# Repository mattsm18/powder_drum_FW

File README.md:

# powder_drum_FW

Firmware for ENME891 - Industrial Project

# About

ENME891 is the capstone paper for the BE(Hons) degree at AUT. It is a year-long industrial project where students develop a real-world engineering solution.

### Project name: 
<b>Quanitfying the flowability of milk powders through the use of computer vision </b>

### Project members / responsibilities:
- Matthew Smith -> Embedded Firmware and Software Development, Mechanical Design, Electronic Design & Assembly
- Josh Russell -> Mechanical build and machining, MATLAB Computer vision modelling.

# Target
### Arduino Nano Every 
Potential for future, more capable targets due to using the PlatformIO framework

# Functionality
- Drive stepper motor from 0.1-70RPM with a closed-loop PID controller
- Control a 5V Relay Module
- Run bi-directional comms over serial to [powder_drum_SW](https://github.com/mattsm18/powder_drum_SW)

# Libraries

### StepperMotor
- Handles pin assignment, microstepping and internal velocity tracking
- Attaches a tick function to an ISR for atomic stepping

### AS5600 (Magnetic Encoder)
- Handles pin assignment and I2C comms with the encoder
- Determines current angular velocity of the motor
- Applies a 1st order discrete time filter

### PIDController
- Wraps all PID Controller functionality
- Handles dynamic Kp, Ki and Kd gains

### SerialManager
- Implements the packet framing protocol (SOF, header, payload, XOR CRC) over serial
- Validates and dispatches incoming GET/SET requests, returning ACK/NACK per the protocol

### PowderDrumProtocol
- Auto-generated from a single JSON source of truth (config/pd_comms_protocol_vX.X.json)
- Provides parameter metadata lookup (existence, access permissions) used by SerialManager

# Dependencies
- Use of the PlatformIO extension in VSCode for compiling, running and debugging code

# System Diagram

# Serial Comms Protocol
The powder drum implements a custom bi-directional serial comms protocol in 
the firmware and the software

This protocol includes ACKs, NACKs and a XOR CRC checksum to validate data integrity on the wire.

Fully implemented in the firmware, some work still to do for ACK and NACK handling in the software.

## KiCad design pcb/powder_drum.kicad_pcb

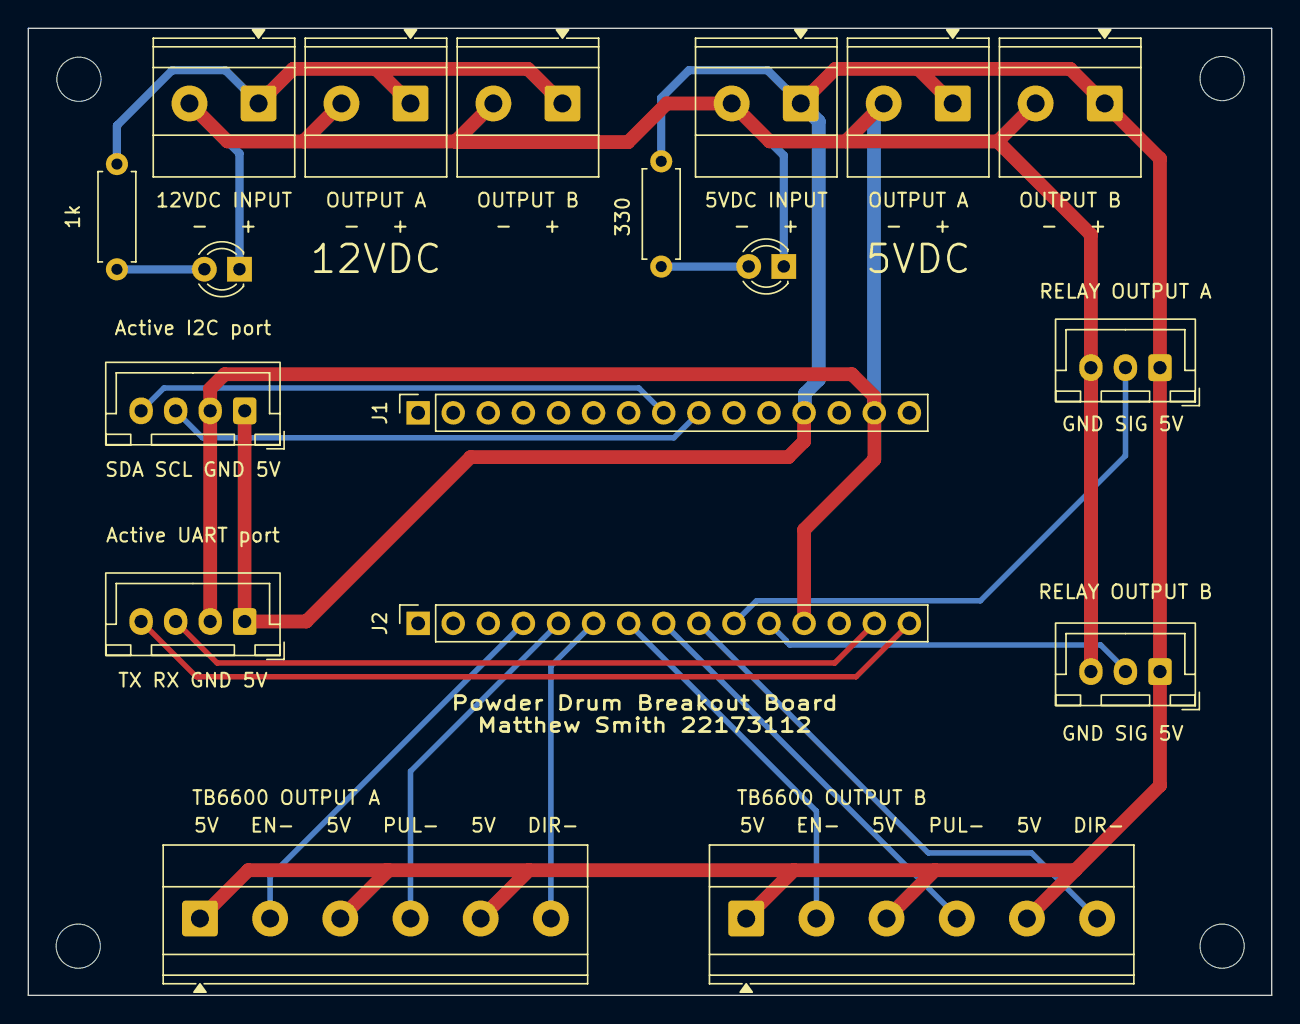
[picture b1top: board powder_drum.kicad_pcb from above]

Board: 2 copper layers, 90.0 x 70.0 mm, 18 parts (0 on the bottom side), 18 nets.

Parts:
D1, D2: LED; LED_D3.0mm
J1: Analog; PinSocket_1x15_P2.54mm_Vertical
J2: Digital; PinSocket_1x15_P2.54mm_Vertical
J3: 12VDC INPUT; TerminalBlock_Phoenix_MKDS-1,5-2_1x02_P5.00mm_Horizontal
J4: 5VDC INPUT; TerminalBlock_Phoenix_MKDS-1,5-2_1x02_P5.00mm_Horizontal
J5: TB6600 OUTPUT A; TerminalBlock_Phoenix_MKDS-1,5-6-5.08_1x06_P5.08mm_Horizont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
J6: TB6600 OUTPUT B; TerminalBlock_Phoenix_MKDS-1,5-6-5.08_1x06_P5.08mm_Horizont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
J7: Active UART port; JST_XH_B4B-XH-A_1x04_P2.50mm_Vertical
J8: RELAY OUTPUT B; JST_XH_B3B-XH-A_1x03_P2.50mm_Vertical
J9: RELAY OUTPUT A; JST_XH_B3B-XH-A_1x03_P2.50mm_Vertical
J10, J12: OUTPUT A; TerminalBlock_Phoenix_MKDS-1,5-2_1x02_P5.00mm_Horizontal
J11, J13: OUTPUT B; TerminalBlock_Phoenix_MKDS-1,5-2_1x02_P5.00mm_Horizontal
J14: Active I2C port; JST_XH_B4B-XH-A_1x04_P2.50mm_Vertical
R1: 330; R_Axial_DIN0207_L6.3mm_D2.5mm_P7.62mm_Horizontal
R2: 1k; R_Axial_DIN0207_L6.3mm_D2.5mm_P7.62mm_Horizontal

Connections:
+5V: J1.12, J4.1, J5.1, J5.3, J5.5, J6.1, J6.3, J6.5, J7.1, J8.1, J9.1, J12.1, J13.1, J14.1, R1.1
+12V: J3.1, J10.1, J11.1, R2.1
/*D3/RELAY A: J2.10, J9.2
/*D5/B PUL-: J2.8, J6.4
/*D6/B ENA-: J2.7, J6.2
/*D9/A ENA-: J2.4, J5.2
/A4/SDA: J1.8, J14.4
/A5/SCL: J1.9, J14.3
/D0/RX: J2.14, J7.3
/D1/TX: J2.15, J7.4
/D2/RELAY B: J2.11, J8.2
/D4/B DIR-: J2.9, J6.6
/D7/A DIR-: J2.6, J5.6
/D8/A PUL-: J2.5, J5.4
/~RESET: J1.13, J2.13
GND: D1.1 (K), D2.1 (K), J1.14, J2.12, J3.2, J4.2, J7.2, J8.3, J9.3, J10.2, J11.2, J12.2, J13.2, J14.2
unnamed: D1.2 (A), R1.2
unnamed: D2.2 (A), R2.2

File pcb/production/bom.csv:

Designator,Footprint,Quantity,Value,LCSC Part #
"D1, D2",LED_D3.0mm,2,LED,
J1,PinSocket_1x15_P2.54mm_Vertical,1,Analog,
"J10, J12","TerminalBlock_Phoenix_MKDS-1,5-2_1x02_P5.00mm_Horizontal",2,OUTPUT A,
"J11, J13","TerminalBlock_Phoenix_MKDS-1,5-2_1x02_P5.00mm_Horizontal",2,OUTPUT B,
J14,JST_XH_B4B-XH-A_1x04_P2.50mm_Vertical,1,Active I2C port,
J2,PinSocket_1x15_P2.54mm_Vertical,1,Digital,
J3,"TerminalBlock_Phoenix_MKDS-1,5-2_1x02_P5.00mm_Horizontal",1,12VDC INPUT,
J4,"TerminalBlock_Phoenix_MKDS-1,5-2_1x02_P5.00mm_Horizontal",1,5VDC INPUT,
J5,"TerminalBlock_Phoenix_MKDS-1,5-6-5.08_1x06_P5.08mm_Horizontal",1,TB6600 OUTPUT A,
J6,"TerminalBlock_Phoenix_MKDS-1,5-6-5.08_1x06_P5.08mm_Horizontal",1,TB6600 OUTPUT B,
J7,JST_XH_B4B-XH-A_1x04_P2.50mm_Vertical,1,Active UART port,
J8,JST_XH_B3B-XH-A_1x03_P2.50mm_Vertical,1,RELAY OUTPUT B,
J9,JST_XH_B3B-XH-A_1x03_P2.50mm_Vertical,1,RELAY OUTPUT A,
R1,R_Axial_DIN0207_L6.3mm_D2.5mm_P7.62mm_Horizontal,1,330,
R2,R_Axial_DIN0207_L6.3mm_D2.5mm_P7.62mm_Horizontal,1,1k,

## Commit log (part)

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2026-04-30 Accurate (ish) as5600 readings - work to do so that higher speeds are more accurate
2026-05-01 Encoder Angular Velocity with EMA filter, decent angular velocity estimation, slightly lagging reality
2026-05-01 Accurate PI Controller Implementation
2026-05-01 Really good speed control
2026-05-06 Functional bidirectional Serial Protocol Implemented with backwards compatibility, versioning and CRC for data integrity
2026-05-06 Changed system to expect IEEE 754 Floats -> Integrated the first version of the comms parameter table
2026-05-06 fixed encoder bug with negative value
2026-05-08 Changed PI Controller params to be configurable at runtime
2026-05-10 Update to 1/32 Microstep w/ 32kHz ISR
2026-05-12 Updated docs and readme
2026-05-12 updated image link
2026-05-12 Updated readme to include about section
2026-06-08 update gitignore
2026-06-08 Removed .vscode from tracking
2026-06-08 Time const for encoder filter changed
